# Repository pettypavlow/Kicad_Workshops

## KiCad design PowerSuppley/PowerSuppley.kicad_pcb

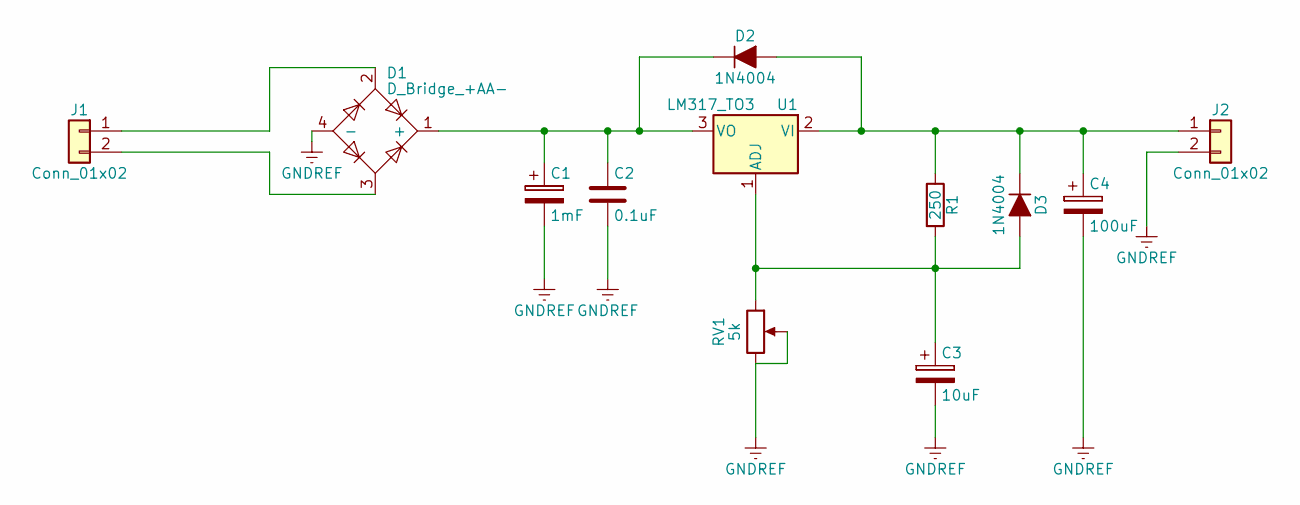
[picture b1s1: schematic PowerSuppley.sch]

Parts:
C1: 1mF; CP_Radial_D6.3mm_P2.50mm
C2: 0.1uF; C_Disc_D6.0mm_W4.4mm_P5.00mm
C3: 10uF; CP_Radial_D4.0mm_P2.00mm
C4: 100uF; CP_Radial_D5.0mm_P2.50mm
D1: D_Bridge_+AA-; Diode_Bridge_18.5x5.5
D2, D3: 1N4004; D_T-1_P5.08mm_Horizontal
J1, J2: Conn_01x02; Pin_Header_Angled_1x02_Pitch2.54mm
R1: 250; R_Axial_DIN0207_L6.3mm_D2.5mm_P10.16mm_Horizontal
RV1: 5k; Potentiometer_VishaySpectrol_248GH_249GH_Vertical
U1: LM317_TO3; TO-3PB__Horizontal

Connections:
GNDREF: C1.2, C2.2, C3.2, C4.2, D1.4 (-), J2.2, RV1.2, RV1.3
unnamed: C1.1, C2.1, D1.1 (+), D2.1 (K), U1.3 (VO)
unnamed: C3.1, D3.2 (A), R1.2, RV1.1, U1.1 (ADJ)
unnamed: C4.1, D2.2 (A), D3.1 (K), J2.1, R1.1, U1.2 (VI)
unnamed: D1.2, J1.1
unnamed: D1.3, J1.2

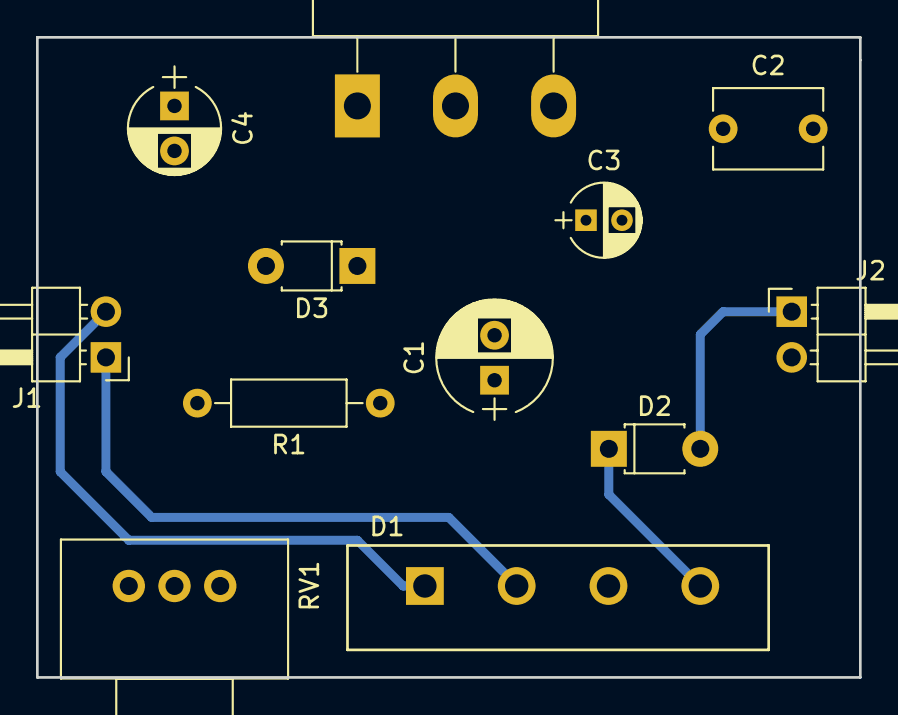
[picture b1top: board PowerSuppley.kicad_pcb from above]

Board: 2 copper layers, 45.7 x 35.6 mm, 12 parts (0 on the bottom side), 6 nets.

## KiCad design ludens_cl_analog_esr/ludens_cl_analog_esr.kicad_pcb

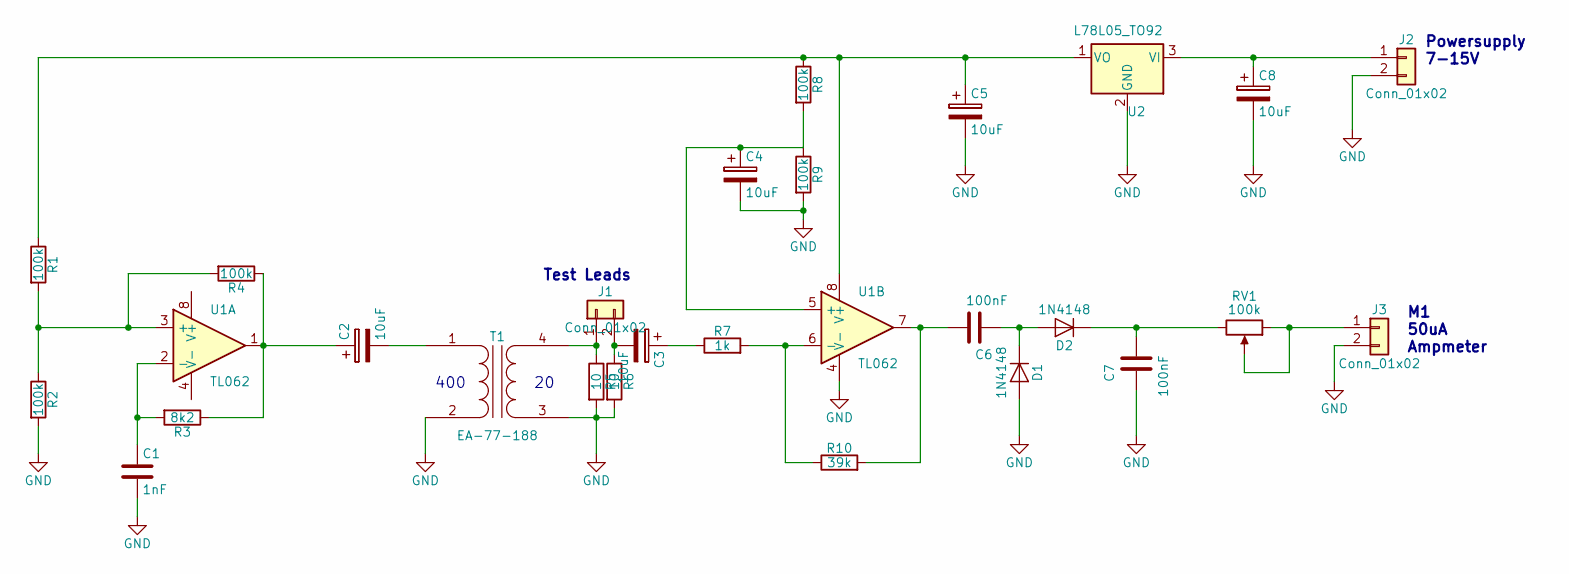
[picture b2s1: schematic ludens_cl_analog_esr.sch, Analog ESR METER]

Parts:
C1: 1nF; C_Axial_L3.8mm_D2.6mm_P15.00mm_Horizontal
C2, C3, C4, C5, C8: 10uF; CP_Radial_D5.0mm_P2.50mm
C6, C7: 100nF; C_Disc_D7.5mm_W2.5mm_P5.00mm
D1, D2: 1N4148; D_DO-35_SOD27_P2.54mm_Vertical_AnodeUp
J1, J2, J3: Conn_01x02; Pin_Header_Angled_1x02_Pitch2.54mm
R1, R2, R4, R8, R9: 100k; R_Axial_DIN0414_L11.9mm_D4.5mm_P5.08mm_Vertical
R3: 8k2; R_Axial_DIN0414_L11.9mm_D4.5mm_P5.08mm_Vertical
R5, R6: 10; R_Axial_DIN0414_L11.9mm_D4.5mm_P5.08mm_Vertical
R7: 1k; R_Axial_DIN0414_L11.9mm_D4.5mm_P5.08mm_Vertical
R10: 39k; R_Axial_DIN0414_L11.9mm_D4.5mm_P5.08mm_Vertical
RV1: 100k; Potentiometer_Alps_RK09Y_Vertical
T1: EA-77-188; Coilcraft-Q4434-B_Rhombus-T1311
U1: TL062; DIP-8_W7.62mm_Socket_LongPads
U2: L78L05_TO92; TO-92_Horizontal1_Inline_Narrow_Oval

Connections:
GND: C1.2, C4.2, C5.2, C7.1, C8.2, D1.2 (A), J2.2, J3.2, R2.2, R5.2, R6.2, R9.2, T1.2 (AB), T1.3 (SA), U1.4 (V-), U2.2 (GND)
unnamed: C1.1, R3.2, U1.2 (-)
unnamed: C2.1, R3.1, R4.1, U1.1
unnamed: C2.2, T1.1 (AA)
unnamed: C3.1, R7.1
unnamed: C3.2, J1.2, R6.1
unnamed: C4.1, R8.2, R9.1, U1.5 (+)
unnamed: C5.1, R1.1, R8.1, U1.8 (V+), U2.1 (VO)
unnamed: C6.1, D1.1 (K), D2.2 (A)
unnamed: C6.2, R10.2, U1.7
unnamed: C7.2, D2.1 (K), RV1.3
unnamed: C8.1, J2.1, U2.3 (VI)
unnamed: J1.1, R5.1, T1.4 (SB)
unnamed: J3.1, RV1.1, RV1.2
unnamed: R1.2, R2.1, R4.2, U1.3 (+)
unnamed: R7.2, R10.1, U1.6 (-)

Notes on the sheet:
400
Powersupply 7-15V
M1 50uA Ampmeter
Test Leads

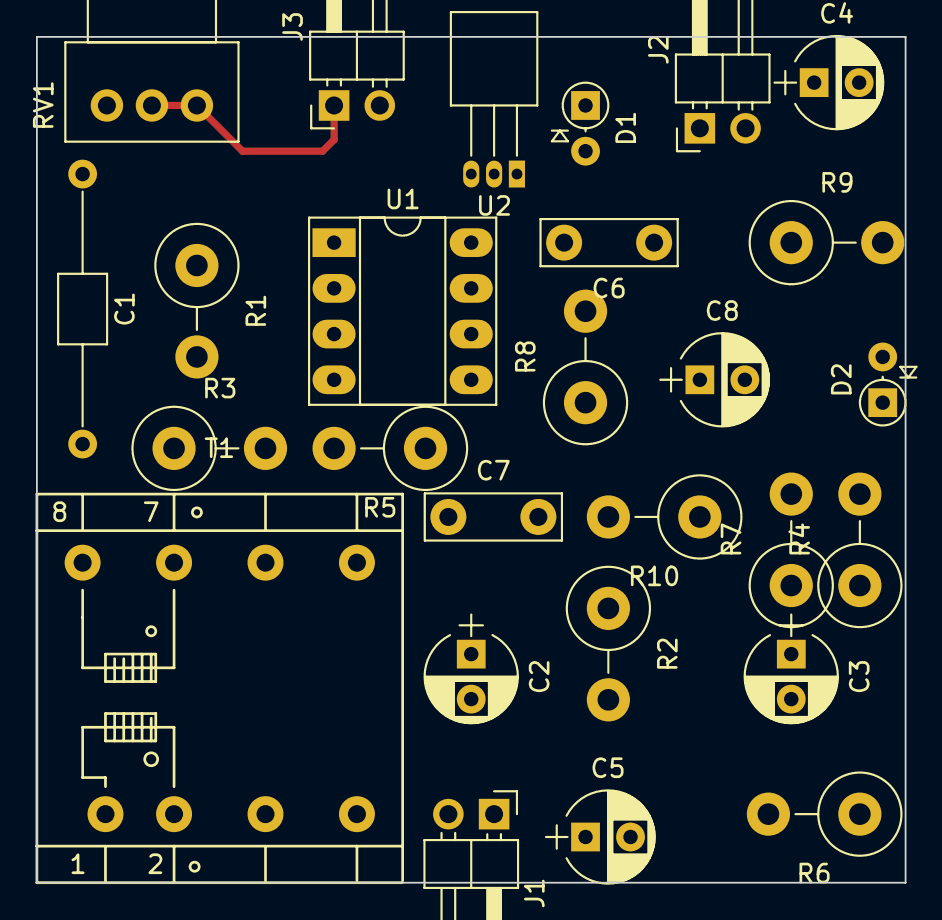
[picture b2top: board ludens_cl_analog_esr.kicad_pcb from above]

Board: 2 copper layers, 48.3 x 47.0 mm, 27 parts (0 on the bottom side), 16 nets.

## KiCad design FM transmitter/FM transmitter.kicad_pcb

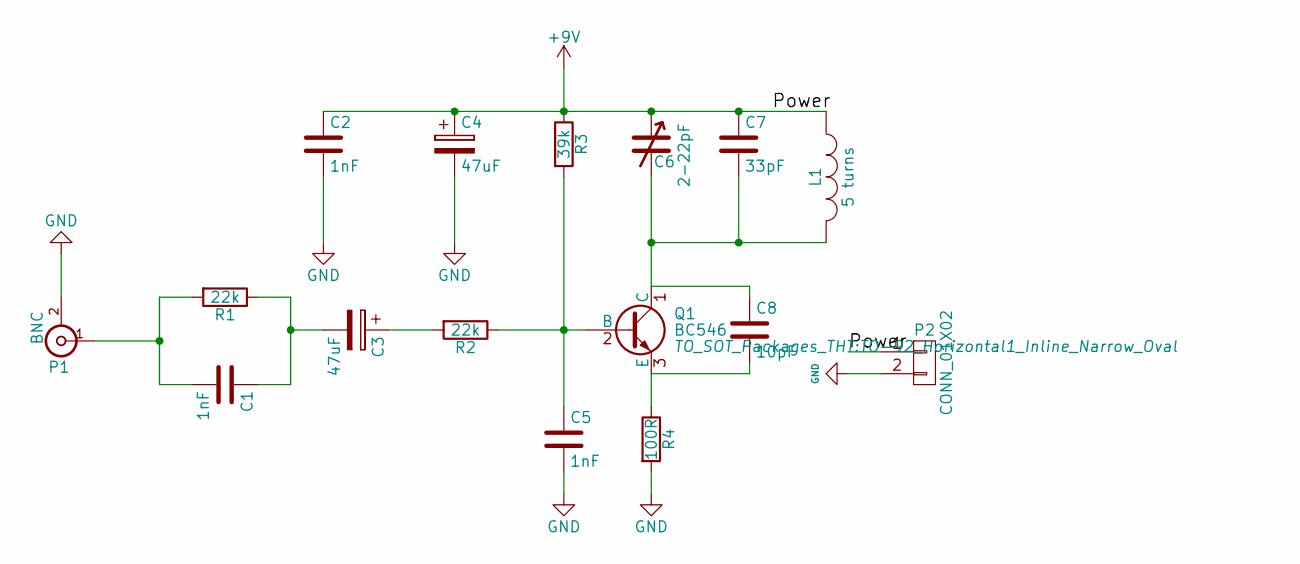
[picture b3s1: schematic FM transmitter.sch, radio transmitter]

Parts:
C1, C2, C5: 1nF; C_Disc_D3_P2.5
C3, C4: 47uF; C_Radial_D5_L11_P2.5
C6: 2-22pF; C_Disc_D3_P2.5
C7: 33pF; C_1825
C8: 10pF; C_1825
L1: 5 turns; Neosid_Air-Coil_SML_5turn_HDM0531A
P1: BNC; BNC_Socket_TYCO-AMP_LargePads
P2: CONN_01X02; Pin_Header_Angled_1x02
Q1: BC546; TO-92_Horizontal1_Inline_Narrow_Oval
R1, R2: 22k; Resistor_Horizontal_RM10mm
R3: 39k; Resistor_Horizontal_RM10mm
R4: 100R; Resistor_Horizontal_RM10mm

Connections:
+9V: C2.1, C4.1, C6.1, C7.1, L1.1, P2.1, R3.1
GND: C2.2, C4.2, C5.2, P1.2 (Ext), P2.2, R4.2
unnamed: C1.1, C3.2, R1.1
unnamed: C1.2, P1.1 (In), R1.2
unnamed: C3.1, R2.2
unnamed: C5.1, Q1.2 (B), R2.1, R3.2
unnamed: C6.2, C7.2, C8.1, L1.2, Q1.1 (C)
unnamed: C8.2, Q1.3 (E), R4.1

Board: 2 copper layers, 16 parts (0 on the bottom side), 8 nets, no tracks yet.

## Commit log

2017-09-21 Repo clone
    Repo clone
2017-09-21 ESr meter 2
    ESr meter 2
2017-09-22 Poti Update
    Poti Update
2017-09-29 Schema Discription Update
    Schema Discription Update
2017-10-08 new things
    new things
2017-10-08 changes
    changes
